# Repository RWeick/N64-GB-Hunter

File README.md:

# N64-GB-Hunter
The Kicad files and Rom dump of the N64 GB Hunter

PCB Thickness: 1.2 mm

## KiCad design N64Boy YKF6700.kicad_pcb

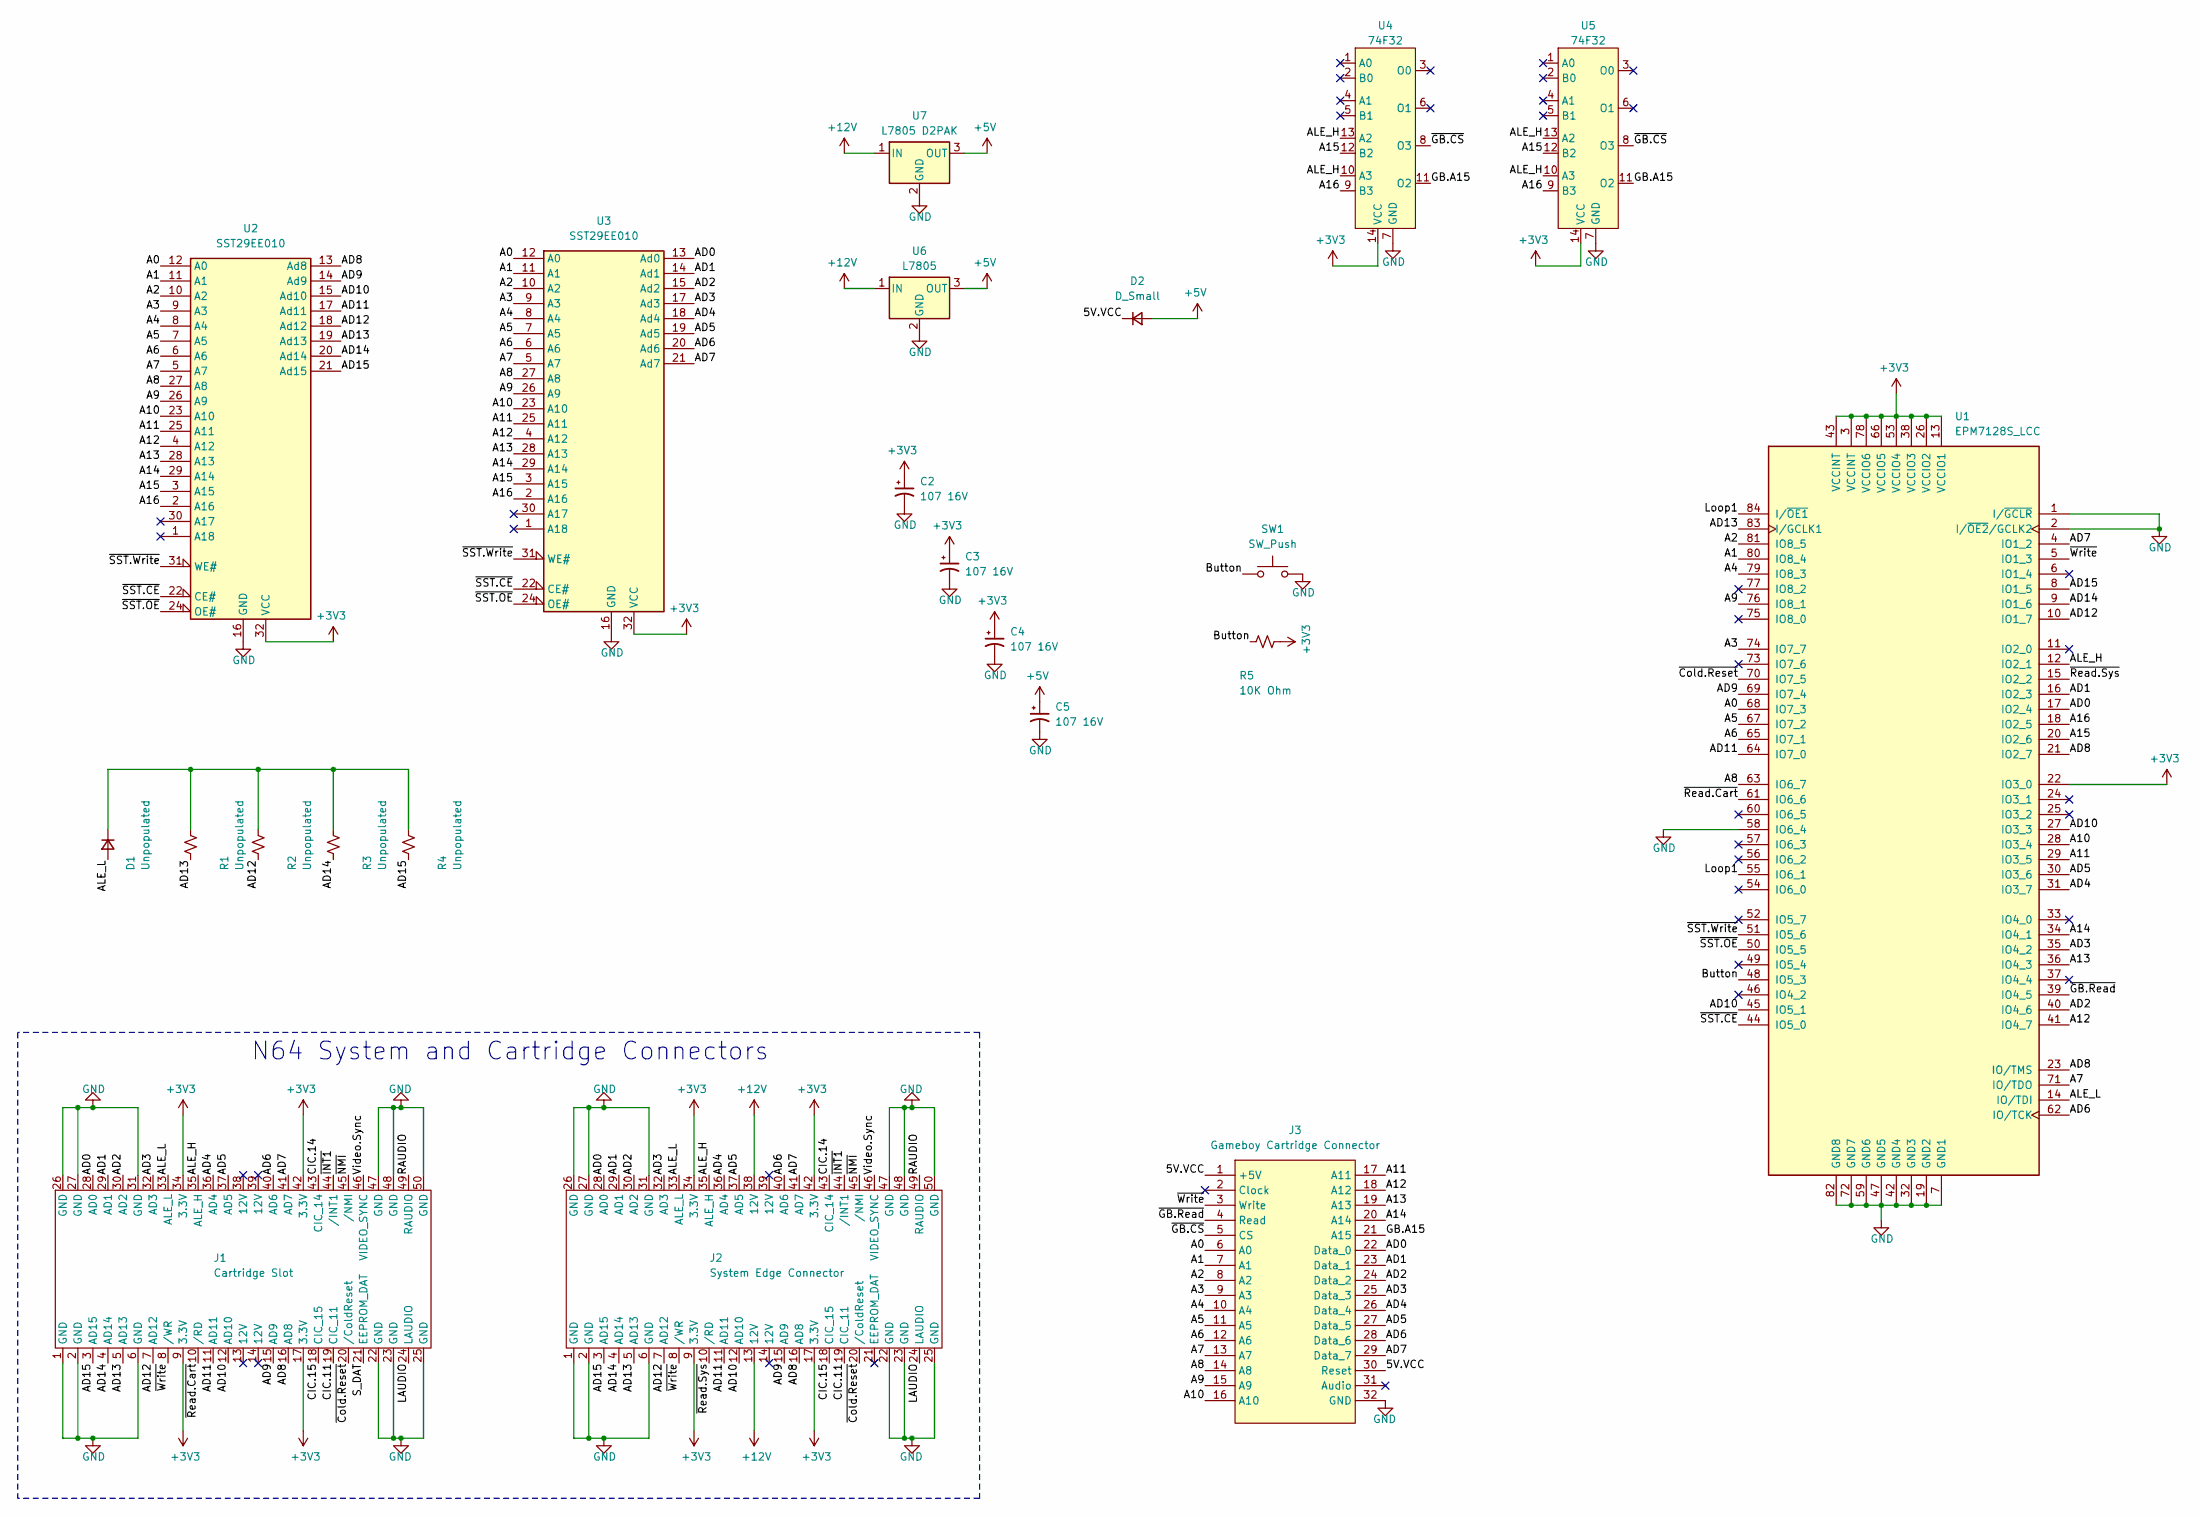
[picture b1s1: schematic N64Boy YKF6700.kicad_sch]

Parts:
C2, C3, C4, C5: 107 16V; Tantalum Caps
D1: Unpopulated; Diode
D2: D_Small; Diode
J1: Cartridge Slot; Middle Connector
J2: System Edge Connector; Edge Connector
J3: Gameboy Cartridge Connector; Gameboy Connector
R1, R2, R3, R4: Unpopulated; 0805 SMD
R5: 10K Ohm; 0805 SMD
SW1: SW_Push; Switch
U1: EPM7128S_LCC; EPM7128
U2, U3: SST29EE010; PLCC32
U4: 74F32; 74F32 SOIC
U5: 74F32; 74F32 DIP14
U6: L7805; LM7805
U7: L7805 D2PAK; LM7805 D2PAK

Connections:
+3V3: C2.1, C3.1, C4.1, J1.9 (3.3V), J1.17 (3.3V), J1.34 (3.3V), J1.42 (3.3V), J2.9 (3.3V), J2.17 (3.3V), J2.34 (3.3V), J2.42 (3.3V), R5.2, U1.3 (VCCINT), U1.13 (VCCIO1), U1.22 (IO3_0), U1.26 (VCCIO2), U1.38 (VCCIO3), U1.43 (VCCINT), U1.53 (VCCIO4), U1.66 (VCCIO5), U1.78 (VCCIO6), U2.32 (VCC), U3.32 (VCC), U4.14 (VCC), U5.14 (VCC)
+5V: C5.1, D2.2 (A), U6.3 (OUT), U7.3 (OUT)
+12V: J2.13 (12V), J2.38 (12V), U6.1 (IN), U7.1 (IN)
/5V.VCC: D2.1 (K), J3.1 (+5V), J3.30 (Reset)
/A0: J3.6 (A0), U1.68 (IO7_3), U2.12 (A0), U3.12 (A0)
/A1: J3.7 (A1), U1.80 (IO8_4), U2.11 (A1), U3.11 (A1)
/A2: J3.8 (A2), U1.81 (IO8_5), U2.10 (A2), U3.10 (A2)
/A3: J3.9 (A3), U1.74 (IO7_7), U2.9 (A3), U3.9 (A3)
/A4: J3.10 (A4), U1.79 (IO8_3), U2.8 (A4), U3.8 (A4)
/A5: J3.11 (A5), U1.67 (IO7_2), U2.7 (A5), U3.7 (A5)
/A6: J3.12 (A6), U1.65 (IO7_1), U2.6 (A6), U3.6 (A6)
/A7: J3.13 (A7), U1.71 (IO/TDO), U2.5 (A7), U3.5 (A7)
/A8: J3.14 (A8), U1.63 (IO6_7), U2.27 (A8), U3.27 (A8)
/A9: J3.15 (A9), U1.76 (IO8_1), U2.26 (A9), U3.26 (A9)
/A10: J3.16 (A10), U1.28 (IO3_4), U2.23 (A10), U3.23 (A10)
/A11: J3.17 (A11), U1.29 (IO3_5), U2.25 (A11), U3.25 (A11)
/A12: J3.18 (A12), U1.41 (IO4_7), U2.4 (A12), U3.4 (A12)
/A13: J3.19 (A13), U1.36 (IO4_3), U2.28 (A13), U3.28 (A13)
/A14: J3.20 (A14), U1.34 (IO4_1), U2.29 (A14), U3.29 (A14)
/A15: U1.20 (IO2_6), U2.3 (A15), U3.3 (A15), U4.12 (B2), U5.12 (B2)
/A16: U1.18 (IO2_5), U2.2 (A16), U3.2 (A16), U4.9 (B3), U5.9 (B3)
/AD0: J1.28 (AD0), J2.28 (AD0), J3.22 (Data_0), U1.17 (IO2_4), U3.13 (Ad0)
/AD1: J1.29 (AD1), J2.29 (AD1), J3.23 (Data_1), U1.16 (IO2_3), U3.14 (Ad1)
/AD2: J1.30 (AD2), J2.30 (AD2), J3.24 (Data_2), U1.40 (IO4_6), U3.15 (Ad2)
/AD3: J1.32 (AD3), J2.32 (AD3), J3.25 (Data_3), U1.35 (IO4_2), U3.17 (Ad3)
/AD4: J1.36 (AD4), J2.36 (AD4), J3.26 (Data_4), U1.31 (IO3_7), U3.18 (Ad4)
/AD5: J1.37 (AD5), J2.37 (AD5), J3.27 (Data_5), U1.30 (IO3_6), U3.19 (Ad5)
/AD6: J1.40 (AD6), J2.40 (AD6), J3.28 (Data_6), U1.62 (IO/TCK), U3.20 (Ad6)
/AD7: J1.41 (AD7), J2.41 (AD7), J3.29 (Data_7), U1.4 (IO1_2), U3.21 (Ad7)
/AD8: J1.16 (AD8), J2.16 (AD8), U1.21 (IO2_7), U1.23 (IO/TMS), U2.13 (Ad8)
/AD9: J1.15 (AD9), J2.15 (AD9), U1.69 (IO7_4), U2.14 (Ad9)
/AD10: J1.12 (AD10), J2.12 (AD10), U1.27 (IO3_3), U1.45 (IO5_1), U2.15 (Ad10)
/AD11: J1.11 (AD11), J2.11 (AD11), U1.64 (IO7_0), U2.17 (Ad11)
/AD12: J1.7 (AD12), J2.7 (AD12), R2.1, U1.10 (IO1_7), U2.18 (Ad12)
/AD13: J1.5 (AD13), J2.5 (AD13), R1.1, U1.83 (I/GCLK1), U2.19 (Ad13)
/AD14: J1.4 (AD14), J2.4 (AD14), R3.1, U1.9 (IO1_6), U2.20 (Ad14)
/AD15: J1.3 (AD15), J2.3 (AD15), R4.1, U1.8 (IO1_5), U2.21 (Ad15)
/ALE_H: J1.35 (ALE_H), J2.35 (ALE_H), U1.12 (IO2_1), U4.10 (A3), U4.13 (A2), U5.10 (A3), U5.13 (A2)
/ALE_L: D1.2 (A), J1.33 (ALE_L), J2.33 (ALE_L), U1.14 (IO/TDI)
/Button: R5.1, SW1.1, U1.48 (IO5_3)
/CIC.11: J1.19 (CIC_11), J2.19 (CIC_11)
/CIC.14: J1.43 (CIC_14), J2.43 (CIC_14)
/CIC.15: J1.18 (CIC_15), J2.18 (CIC_15)
/GB.A15: J3.21 (A15), U4.11 (O2), U5.11 (O2)
/LAUDIO: J1.24 (LAUDIO), J2.24 (LAUDIO)
/Loop1: U1.55 (IO6_1), U1.84 (I/~OE1)
/RAUDIO: J1.49 (RAUDIO), J2.49 (RAUDIO)
/S_DAT: J1.21 (EEPROM_DAT)
/Video.Sync: J1.46 (VIDEO_SYNC), J2.46 (VIDEO_SYNC)
/~Cold.Reset: J1.20 (/ColdReset), J2.20 (/ColdReset), U1.70 (IO7_5)
/~GB.CS: J3.5 (CS), U4.8 (O3), U5.8 (O3)
/~GB.Read: J3.4 (Read), U1.39 (IO4_5)
/~INT1: J1.44 (/INT1), J2.44 (/INT1)
/~NMI: J1.45 (/NMI), J2.45 (/NMI)
/~Read.Cart: J1.10 (/RD), U1.61 (IO6_6)
/~Read.Sys: J2.10 (/RD), U1.15 (IO2_2)
/~SST.CE: U1.44 (IO5_0), U2.22 (CE#), U3.22 (CE#)
/~SST.OE: U1.50 (IO5_5), U2.24 (OE#), U3.24 (OE#)
/~SST.Write: U1.51 (IO5_6), U2.31 (WE#), U3.31 (WE#)
/~Write: J1.8 (/WR), J2.8 (/WR), J3.3 (Write), U1.5 (IO1_3)
GND: C2.2, C3.2, C4.2, C5.2, J1.1 (GND), J1.2 (GND), J1.6 (GND), J1.22 (GND), J1.23 (GND), J1.25 (GND), J1.26 (GND), J1.27 (GND), J1.31 (GND), J1.47 (GND), J1.48 (GND), J1.50 (GND), J2.1 (GND), J2.2 (GND), J2.6 (GND), J2.22 (GND), J2.23 (GND), J2.25 (GND), J2.26 (GND), J2.27 (GND), J2.31 (GND), J2.47 (GND), J2.48 (GND), J2.50 (GND), J3.32 (GND), SW1.2, U1.1 (I/~GCLR), U1.2 (I/~OE2/GCLK2), U1.7 (GND1), U1.19 (GND2), U1.32 (GND3), U1.42 (GND4), U1.47 (GND5), U1.58 (IO6_4), U1.59 (GND6), U1.72 (GND7), U1.82 (GND8), U2.16 (GND), U3.16 (GND), U4.7 (GND), U5.7 (GND), U6.2 (GND), U7.2 (GND)
unnamed: D1.1 (K), R1.2, R2.2, R3.2, R4.2

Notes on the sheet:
N64 System and Cartridge Connectors

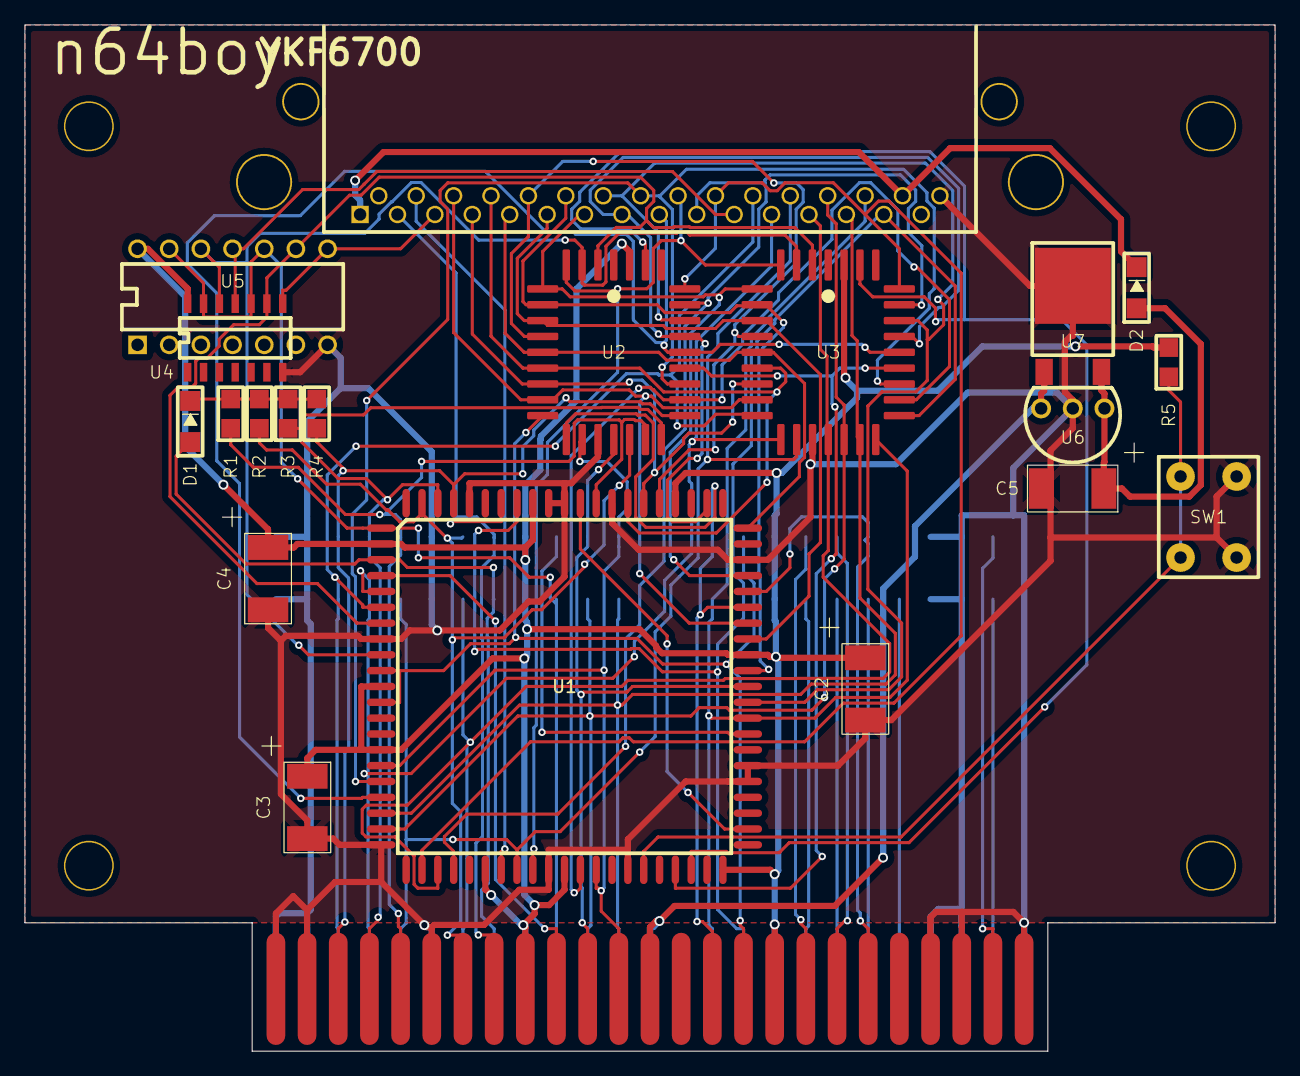
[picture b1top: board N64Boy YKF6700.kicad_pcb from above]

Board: 2 copper layers, 100.2 x 82.3 mm, 23 parts (0 on the bottom side), 61 nets.

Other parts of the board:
Holes: Drill Holes
